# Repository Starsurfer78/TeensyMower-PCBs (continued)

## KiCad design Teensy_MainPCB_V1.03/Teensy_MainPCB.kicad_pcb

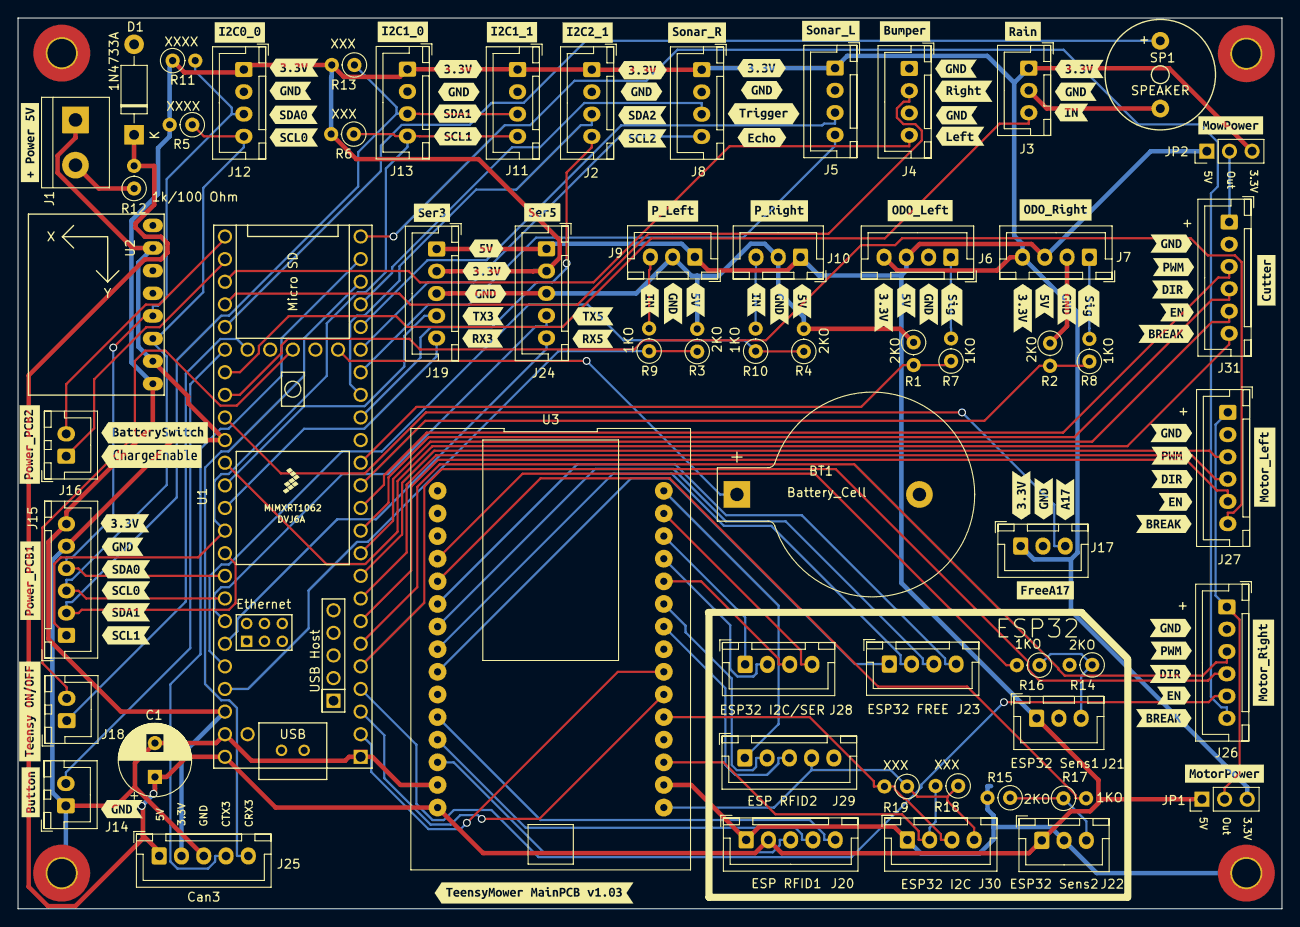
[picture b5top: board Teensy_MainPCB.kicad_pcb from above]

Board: 2 copper layers, 141.9 x 100.0 mm, 160 parts (0 on the bottom side), 76 nets.

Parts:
BT1: Battery_Cell; BatteryHolder_Keystone_103_1x20mm
C1: CP1; CP_Radial_D8.0mm_P3.80mm
D1: 1N4733A; D_DO-41_SOD81_P10.16mm_Horizontal
H1, H2, H3, H4: MountingHole_Pad; MountingHole_3.2mm_M3_Pad_TopBottom
J1: 5V IN; TerminalBlock_bornier-2_P5.08mm
J2: I2C2_0; JST_XH_B4B-XH-A_1x04_P2.50mm_Vertical
J3: Rain; JST_XH_B3B-XH-A_1x03_P2.50mm_Vertical
J4: Bumper; JST_XH_B4B-XH-A_1x04_P2.50mm_Vertical
J5: Sonar_L; JST_XH_B4B-XH-A_1x04_P2.50mm_Vertical
J6: ODO_Left; JST_XH_B4B-XH-A_1x04_P2.50mm_Vertical
J7: ODO_Right; JST_XH_B4B-XH-A_1x04_P2.50mm_Vertical
J8: Sonar_R; JST_XH_B4B-XH-A_1x04_P2.50mm_Vertical
J9: P_Left; JST_XH_B3B-XH-A_1x03_P2.50mm_Vertical
J10: P_Right; JST_XH_B3B-XH-A_1x03_P2.50mm_Vertical
J11: I2C1_1; JST_XH_B4B-XH-A_1x04_P2.50mm_Vertical
J12: I2C0_0; JST_XH_B4B-XH-A_1x04_P2.50mm_Vertical
J13: I2C1_0; JST_XH_B4B-XH-A_1x04_P2.50mm_Vertical
J14: Button; JST_XH_B2B-XH-A_1x02_P2.50mm_Vertical
J15: Power_PCB1; JST_XH_B6B-XH-A_1x06_P2.50mm_Vertical
J16: Power_PCB2; JST_XH_B2B-XH-A_1x02_P2.50mm_Vertical
J17: FreeA17; JST_XH_B3B-XH-A_1x03_P2.50mm_Vertical
J18: Teensy On/Off; JST_XH_B2B-XH-A_1x02_P2.50mm_Vertical
J19: Ser3; JST_XH_B5B-XH-A_1x05_P2.50mm_Vertical
J20: ESP RFID1; JST_XH_B5B-XH-A_1x05_P2.50mm_Vertical
J21: ESP32 Sens1; JST_XH_B3B-XH-A_1x03_P2.50mm_Vertical
J22: ESP32 Sens2; JST_XH_B3B-XH-A_1x03_P2.50mm_Vertical
J23: ESP32 FREE; JST_XH_B4B-XH-A_1x04_P2.50mm_Vertical
J24: Ser5; JST_XH_B5B-XH-A_1x05_P2.50mm_Vertical
J25: Can3; JST_XH_B5B-XH-A_1x05_P2.50mm_Vertical
J26: Motor_Right; JST_XH_B6B-XH-A_1x06_P2.50mm_Vertical
J27: Motor_Left; JST_XH_B6B-XH-A_1x06_P2.50mm_Vertical
J28: ESP32 I2C/SER; JST_XH_B4B-XH-A_1x04_P2.50mm_Vertical
J29: ESP RFID2; JST_XH_B5B-XH-A_1x05_P2.50mm_Vertical
J30: ESP32 I2C; JST_XH_B4B-XH-A_1x04_P2.50mm_Vertical
J31: Cutter; JST_XH_B6B-XH-A_1x06_P2.50mm_Vertical
JP1: MotorPower; PinHeader_1x03_P2.54mm_Vertical
JP2: CutterPower; PinHeader_1x03_P2.54mm_Vertical
R1, R2, R3, R4, R14, R15: 2KO; R_Axial_DIN0207_L6.3mm_D2.5mm_P2.54mm_Vertical
R5, R11: XXXX; R_Axial_DIN0207_L6.3mm_D2.5mm_P2.54mm_Vertical
R6, R13, R18, R19: XXX; R_Axial_DIN0207_L6.3mm_D2.5mm_P2.54mm_Vertical
R7, R8, R9, R10, R16, R17: 1KO; R_Axial_DIN0207_L6.3mm_D2.5mm_P2.54mm_Vertical
R12: 1k/100 Ohm; R_Axial_DIN0207_L6.3mm_D2.5mm_P2.54mm_Vertical
SP1: SPEAKER; Buzzer_12x9.5RM7.6
U1: Teensy4.1; Teensy41
U2: GY-521
U3: ESP32-DEVKIT-V1
kibuzzard-62AA1DDF: G***; kibuzzard-62AA1DDF
kibuzzard-62AA1E85: G***; kibuzzard-62AA1E85
kibuzzard-62AA1F05: G***; kibuzzard-62AA1F05
kibuzzard-62AA3A43: G***; kibuzzard-62AA3A43
kibuzzard-62AA3A85: G***; kibuzzard-62AA3A85
kibuzzard-62AA3B12: G***; kibuzzard-62AA3B12
kibuzzard-62AA34D8: G***; kibuzzard-62AA34D8
kibuzzard-62AA39DC: G***; kibuzzard-62AA39DC
kibuzzard-62AA347B: G***; kibuzzard-62AA347B
kibuzzard-62AA353C: G***; kibuzzard-62AA353C
kibuzzard-62AA3447: G***; kibuzzard-62AA3447
kibuzzard-62AA3566: G***; kibuzzard-62AA3566
kibuzzard-62AB5E06: G***; kibuzzard-62AB5E06
kibuzzard-62AB5E66: G***; kibuzzard-62AB5E66
kibuzzard-62AB5ED1: G***; kibuzzard-62AB5ED1
kibuzzard-62AB5F2F: G***; kibuzzard-62AB5F2F
kibuzzard-62AB5F67: G***; kibuzzard-62AB5F67
kibuzzard-62AB5FC4: G***; kibuzzard-62AB5FC4
kibuzzard-62AB5FF2: G***; kibuzzard-62AB5FF2
kibuzzard-62AB6A77: G***; kibuzzard-62AB6A77
kibuzzard-62AB6A93: G***; kibuzzard-62AB6A93
kibuzzard-62AB6AFA: G***; kibuzzard-62AB6AFA
kibuzzard-62AB6B3D: G***; kibuzzard-62AB6B3D
kibuzzard-62AB6B9B: G***; kibuzzard-62AB6B9B
kibuzzard-62AB6BA8: G***; kibuzzard-62AB6BA8
kibuzzard-62AB6BF4: G***; kibuzzard-62AB6BF4
kibuzzard-62AB6CC8: G***; kibuzzard-62AB6CC8
kibuzzard-62AB6D7A: G***; kibuzzard-62AB6D7A
kibuzzard-62AB6EF0: G***; kibuzzard-62AB6EF0
kibuzzard-62AB6F91: G***; kibuzzard-62AB6F91
kibuzzard-62AB60B1: G***; kibuzzard-62AB60B1
kibuzzard-62AB62B6: G***; kibuzzard-62AB62B6
kibuzzard-62AB62D3: G***; kibuzzard-62AB62D3
kibuzzard-62AB63D2: G***; kibuzzard-62AB63D2
kibuzzard-62AB64C2: G***; kibuzzard-62AB64C2
kibuzzard-62AB64F2: G***; kibuzzard-62AB64F2
kibuzzard-62AB77E5: G***; kibuzzard-62AB77E5
kibuzzard-62AB634F: G***; kibuzzard-62AB634F
kibuzzard-62AB639B: G***; kibuzzard-62AB639B
kibuzzard-62AB756D: G***; kibuzzard-62AB756D
kibuzzard-62AB767F: G***; kibuzzard-62AB767F
kibuzzard-62AB774A: G***; kibuzzard-62AB774A
kibuzzard-62AB778D: G***; kibuzzard-62AB778D
kibuzzard-62AB789F: G***; kibuzzard-62AB789F
kibuzzard-62AB6021: G***; kibuzzard-62AB6021
kibuzzard-62AB6109: G***; kibuzzard-62AB6109
kibuzzard-62AB6374: G***; kibuzzard-62AB6374
kibuzzard-62AB6557: G***; kibuzzard-62AB6557
kibuzzard-62AB7031: G***; kibuzzard-62AB7031
kibuzzard-62AC4CEE: G***; kibuzzard-62AC4CEE
kibuzzard-62AC4D6D: G***; kibuzzard-62AC4D6D
kibuzzard-62AC8CBD: G***; kibuzzard-62AC8CBD
kibuzzard-62AC8CC8: G***; kibuzzard-62AC8CC8
kibuzzard-62AC8CD7: G***; kibuzzard-62AC8CD7
kibuzzard-62AC8CE7: G***; kibuzzard-62AC8CE7
kibuzzard-62AC8CFB: G***; kibuzzard-62AC8CFB
kibuzzard-62AC8D1B: G***; kibuzzard-62AC8D1B
kibuzzard-62AC8D10: G***; kibuzzard-62AC8D10
kibuzzard-62AC8D87: G***; kibuzzard-62AC8D87
kibuzzard-62AC8DAF: G***; kibuzzard-62AC8DAF
kibuzzard-62AC8DEE: G***; kibuzzard-62AC8DEE
kibuzzard-62AC8E7D: G***; kibuzzard-62AC8E7D
kibuzzard-62AC8E96: G***; kibuzzard-62AC8E96
kibuzzard-62AC8EE6: G***; kibuzzard-62AC8EE6
kibuzzard-62AC8F0E: G***; kibuzzard-62AC8F0E
kibuzzard-62AC8F57: G***; kibuzzard-62AC8F57
kibuzzard-62AC8F80: G***; kibuzzard-62AC8F80
kibuzzard-62AC8F92: G***; kibuzzard-62AC8F92
kibuzzard-62AC8FB5: G***; kibuzzard-62AC8FB5
kibuzzard-62AC8FDD: G***; kibuzzard-62AC8FDD
kibuzzard-62AC8FEE: G***; kibuzzard-62AC8FEE
kibuzzard-62AC52F4: G***; kibuzzard-62AC52F4
kibuzzard-62AC90B9: G***; kibuzzard-62AC90B9
kibuzzard-62AC90FB: G***; kibuzzard-62AC90FB
kibuzzard-62AC91A3: G***; kibuzzard-62AC91A3
kibuzzard-62AC91BB: G***; kibuzzard-62AC91BB
kibuzzard-62AC91C5: G***; kibuzzard-62AC91C5
kibuzzard-62AC91DF: G***; kibuzzard-62AC91DF
kibuzzard-62AC91F0: G***; kibuzzard-62AC91F0
kibuzzard-62AC92C8: G***; kibuzzard-62AC92C8
kibuzzard-62AC93D0: G***; kibuzzard-62AC93D0
kibuzzard-62AC95A7: G***; kibuzzard-62AC95A7
kibuzzard-62AC95BD: G***; kibuzzard-62AC95BD
kibuzzard-62AC95C9: G***; kibuzzard-62AC95C9
kibuzzard-62AC916E: G***; kibuzzard-62AC916E
kibuzzard-62AC917A: G***; kibuzzard-62AC917A
kibuzzard-62AC918B: G***; kibuzzard-62AC918B
kibuzzard-62AC932E: G***; kibuzzard-62AC932E
kibuzzard-62AC961B: G***; kibuzzard-62AC961B
kibuzzard-62AC9112: G***; kibuzzard-62AC9112
kibuzzard-62AC9161: G***; kibuzzard-62AC9161
kibuzzard-62AC9196: G***; kibuzzard-62AC9196
kibuzzard-62AC9203: G***; kibuzzard-62AC9203
kibuzzard-62AC9315: G***; kibuzzard-62AC9315
kibuzzard-62AC9376: G***; kibuzzard-62AC9376
kibuzzard-62AC9630: G***; kibuzzard-62AC9630
kibuzzard-62AC9639: G***; kibuzzard-62AC9639

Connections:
+3V3: J2.1, J3.1, J5.1, J6.4, J7.4, J8.1, J11.1, J12.1, J13.1, J15.6, J17.1, J19.2, J24.2, J25.2, JP1.3, JP2.3, R5.2, R6.2, R11.1, R13.2, U1.46 (3V3), U2.1 (VCC)
+5V: C1.1, D1.1 (K), J6.3, J7.3, J9.1, J10.1, J19.1, J20.2, J21.1, J22.1, J24.1, J25.1, JP1.1, JP2.1, R12.2, U1.48 (VIN), U3.15 (VIN)
CRX3: J25.5, U1.22 (30_CRX3)
CTX3: J25.4, U1.23 (31_CTX3)
FreeA17: J17.3, U1.33 (41_A17)
GND: BT1.2 (-), C1.2, D1.2 (A), H1.1, H2.1, H3.1, H4.1, J1.1, J2.2, J3.2, J4.1, J4.3, J5.2, J6.2, J7.2, J8.2, J9.2, J10.2, J11.2, J12.2, J13.2, J14.1, J15.5, J17.2, J19.3, J20.1, J21.2, J22.2, J24.3, J25.3, J26.2, J27.2, J30.1, J31.2, R1.1, R2.1, R3.2, R4.2, R14.2, R15.2, SP1.1, U1.1 (GND), U1.34 (GND), U1.47 (GND), U2.2 (GND), U2.7 (AD0), U3.14 (GND), U3.17 (GND)
unnamed: BT1.1 (+), U1.50 (VBAT)
unnamed: J1.2, R12.1
unnamed: J6.1, R7.2
unnamed: J7.1, R8.2
unnamed: J9.3, R9.2
unnamed: J10.3, R10.2
unnamed: J18.1, U1.54 (ON_OFF)
unnamed: J18.2, U1.52 (GND)
unnamed: J20.3, U3.13 (GPIO13_ADC2-CH4_HSPI-MOSI_RTC-GPIO14)
unnamed: J20.4, U3.12 (GPIO12_ADC2-CH5_HSPI-MISO_RTC-GPIO15)
unnamed: J20.5, U3.11 (GPIO14_ADC2-CH6_HSPI-CLK_RTC-GPIO16)
unnamed: J21.3, R14.1, R16.1
unnamed: J22.3, R15.1, R17.1
unnamed: J23.1, U3.9 (GPIO26_ADC2-CH9_DAC2_RTC-GPIO7)
unnamed: J23.2, U3.8 (GPIO25_ADC2-CH8_DAC1_RTC-GPIO6)
unnamed: J23.3, U3.7 (GPIO33_ADC1-CH5_RTC-GPIO8)
unnamed: J23.4, U3.6 (GPIO32_ADC1-CH4_RTC-GPIO9)
unnamed: J26.1, J27.1, JP1.2
unnamed: J28.1, U3.28 (GPIO1_UART0-TX)
unnamed: J28.2, U3.27 (GPIO3__UART0-RX)
unnamed: J28.3, U3.26 (GPIO21_I2C-SDA)
unnamed: J28.4, U3.29 (GPIO22_I2C-SCL)
unnamed: J29.1, U3.30 (GPIO23_VSPI-MOSI)
unnamed: J29.2, U3.25 (GPIO19_VSPI-MISO)
unnamed: J29.3, U3.24 (GPIO18_VSPI-CLK)
unnamed: J29.4, J30.4, R18.1, R19.1, U3.16 (3V3)
unnamed: J30.2, R18.2, U3.18 (GPIO15_ADC2-CH3_HSPI-CS0_RTC-GPIO13)
unnamed: J30.3, R19.2, U3.20 (GPIO4_ADC2-CH0_RTC-GPIO10)
unnamed: J31.1, JP2.2
unnamed: R16.2, U3.4 (GPIO34_ADC1-CH6_RTC-GPIO4)
unnamed: R17.2, U3.5 (GPIO35_ADC1-CH7_RTC-GPIO5)
RX1: U1.2 (0_RX1_CRX2_CS1), U3.22 (TX2)
RX3: J19.5, U1.37 (15_A1_RX3_SPDIF_IN)
RX5: J24.5, U1.43 (21_A7_RX5_BCLK1)
SCL0: J12.4, J15.3, R5.1, U1.41 (19_A5_SCL), U2.3 (SCL)
SCL1: J11.4, J13.4, J15.1, R6.1, U1.38 (16_A2_RX4_SCL1)
SCL2: J2.4, U1.16 (24_A10_TX6_SCL2)
SDA0: J12.3, J15.4, R11.2, U1.40 (18_A4_SDA), U2.4 (SDA)
SDA1: J11.3, J13.3, J15.2, R13.1, U1.39 (17_A3_TX4_SDA1)
SDA2: J2.3, U1.17 (25_A11_RX6_SDA2)
TX1: U1.3 (1_TX1_CTX2_MISO1), U3.21 (RX2)
TX3: J19.4, U1.36 (14_A0_TX3_SPDIF_OUT)
TX5: J24.4, U1.42 (20_A6_TX5_LRCLK1)
pinBatterySwitch: J16.2, U1.25 (33_MCLK2)
pinBumperLeft: J4.4, U1.27 (35_TX8)
pinBumperRight: J4.2, U1.28 (36_CS)
pinButton: J14.2, U1.30 (38_CS1_IN1)
pinBuzzer: SP1.2, U1.29 (37_CS)
pinChargeEnable: J16.1, U1.26 (34_RX8)
pinMotorLeftBreak: J27.6, U1.32 (40_A16)
pinMotorLeftDir: J27.4, U1.8 (6_OUT1D)
pinMotorLeftEnable: J27.5, U1.7 (5_IN2)
pinMotorLeftPWM: J27.3, U1.9 (7_RX2_OUT1A)
pinMotorMowBreak: J31.6, U1.35 (13_SCK_LED)
pinMotorMowDir: J31.4, U1.11 (9_OUT1C)
pinMotorMowEnable: J31.5, U1.10 (8_TX2_IN1)
pinMotorMowPWM: J31.3, U1.12 (10_CS_MQSR)
pinMotorRightBreak: J26.6, U1.24 (32_OUT1B)
pinMotorRightDir: J26.4, U1.5 (3_LRCLK2)
pinMotorRightEnable: J26.5, U1.4 (2_OUT2)
pinMotorRightPWM: J26.3, U1.6 (4_BCLK2)
pinOdometryLeft: R1.2, R7.1, U1.14 (12_MISO_MQSL)
pinOdometryRight: R2.2, R8.1, U1.13 (11_MOSI_CTX1)
pinPerimeterLeft: R3.1, R9.1, U1.45 (23_A9_CRX1_MCLK1)
pinPerimeterRight: R4.1, R10.1, U1.44 (22_A8_CTX1)
pinRain: J3.3, U1.31 (39_MISO1_OUT1A)
pinSonarLeftEcho: J5.4, U1.18 (26_A12_MOSI1)
pinSonarLeftTrigger: J5.3, U1.20 (28_RX7)
pinSonarRightEcho: J8.4, U1.19 (27_A13_SCK1)
pinSonarRightTrigger: J8.3, U1.21 (29_TX7)

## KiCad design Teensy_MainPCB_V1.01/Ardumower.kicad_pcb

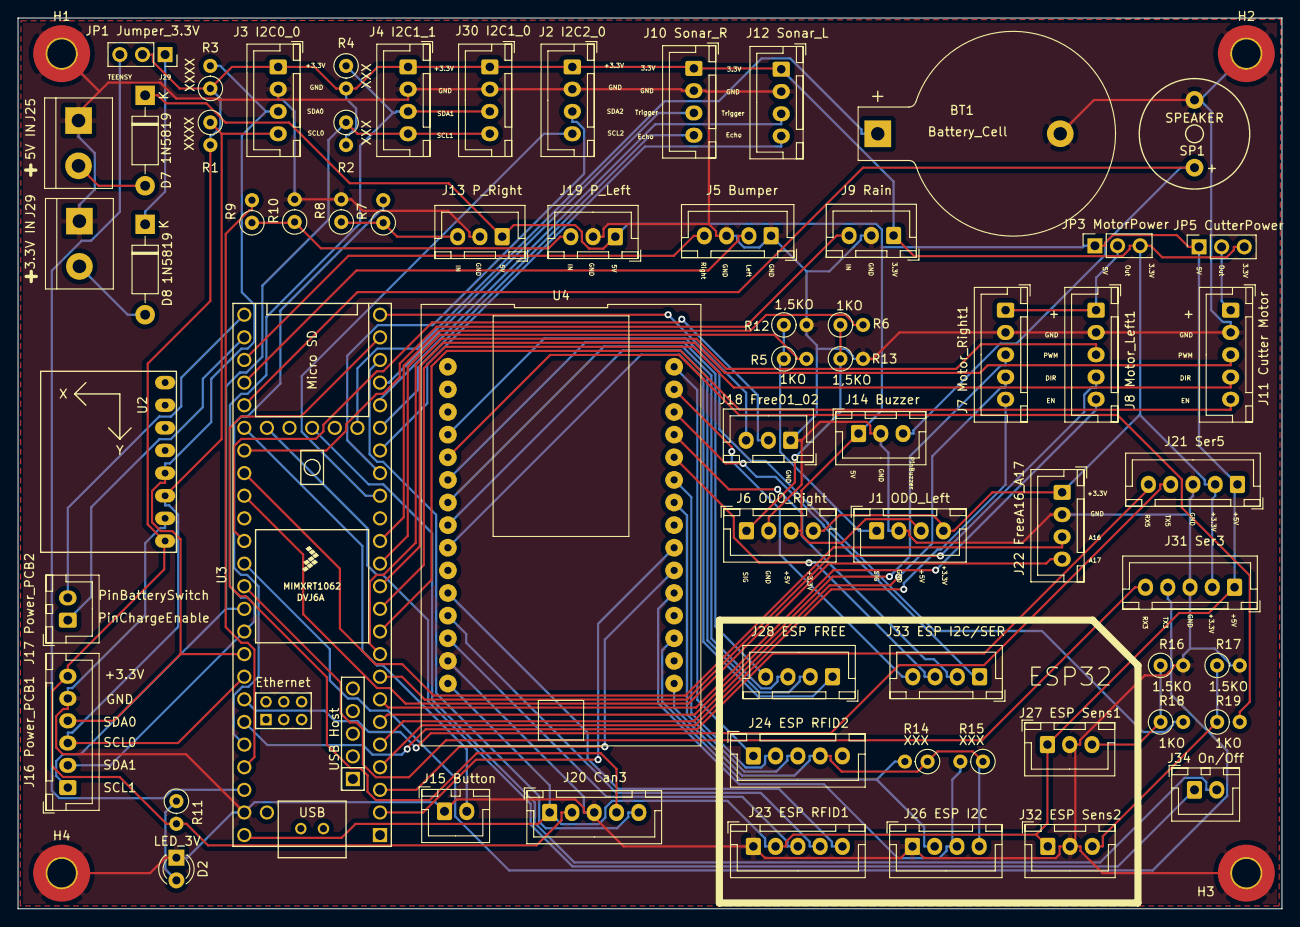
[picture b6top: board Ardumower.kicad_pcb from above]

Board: 2 copper layers, 141.9 x 100.0 mm, 68 parts (0 on the bottom side), 80 nets.

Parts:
BT1: Battery_Cell; BatteryHolder_Keystone_103_1x20mm
D2: LED_3V; LED_D3.0mm
D7, D8: 1N5819; D_DO-41_SOD81_P10.16mm_Horizontal
H1, H2, H3, H4: MountingHole_Pad; MountingHole_3.2mm_M3_Pad_TopBottom
J1 ODO_Left: ODO_Left; JST_XH_B4B-XH-A_1x04_P2.50mm_Vertical
J2 I2C2_0: I2C2_0; JST_XH_B4B-XH-A_1x04_P2.50mm_Vertical
J3 I2C0_0: I2C0_0; JST_XH_B4B-XH-A_1x04_P2.50mm_Vertical
J4 I2C1_1: I2C1_1; JST_XH_B4B-XH-A_1x04_P2.50mm_Vertical
J5 Bumper: Bumper; JST_XH_B4B-XH-A_1x04_P2.50mm_Vertical
J6 ODO_Right: ODO_Right; JST_XH_B4B-XH-A_1x04_P2.50mm_Vertical
J7 Motor_Right1: Motor_Right1; JST_XH_B5B-XH-A_1x05_P2.50mm_Vertical
J8 Motor_Left1: Motor_Left1; JST_XH_B5B-XH-A_1x05_P2.50mm_Vertical
J9 Rain: Rain; JST_XH_B3B-XH-A_1x03_P2.50mm_Vertical
J10 Sonar_R: Sonar_R; JST_XH_B4B-XH-A_1x04_P2.50mm_Vertical
J11 Cutter Motor: Cutter; JST_XH_B5B-XH-A_1x05_P2.50mm_Vertical
J12 Sonar_L: Sonar_L; JST_XH_B4B-XH-A_1x04_P2.50mm_Vertical
J13 P_Right: P_Right; JST_XH_B3B-XH-A_1x03_P2.50mm_Vertical
J14 Buzzer: Buzzer; JST_XH_B3B-XH-A_1x03_P2.50mm_Vertical
J15 Button: Button; JST_XH_B2B-XH-A_1x02_P2.50mm_Vertical
J16 Power_PCB1: Power_PCB1; JST_XH_B6B-XH-A_1x06_P2.50mm_Vertical
J17 Power_PCB2: Power_PCB2; JST_XH_B2B-XH-A_1x02_P2.50mm_Vertical
J18 Free01_02: Free01_02; JST_XH_B3B-XH-A_1x03_P2.50mm_Vertical
J19 P_Left: P_Left; JST_XH_B3B-XH-A_1x03_P2.50mm_Vertical
J20 Can3: Can3; JST_XH_B5B-XH-A_1x05_P2.50mm_Vertical
J21 Ser5: Ser5; JST_XH_B5B-XH-A_1x05_P2.50mm_Vertical
J22 FreeA16_A17: FreeA16_A17; JST_XH_B4B-XH-A_1x04_P2.50mm_Vertical
J23 ESP RFID1: ESP RFID1; JST_XH_B5B-XH-A_1x05_P2.50mm_Vertical
J24 ESP RFID2: ESP RFID2; JST_XH_B5B-XH-A_1x05_P2.50mm_Vertical
J25: 5V IN; TerminalBlock_bornier-2_P5.08mm
J26 ESP I2C: ESP32 I2C; JST_XH_B4B-XH-A_1x04_P2.50mm_Vertical
J27 ESP Sens1: ESP32 Sens1; JST_XH_B3B-XH-A_1x03_P2.50mm_Vertical
J28 ESP FREE: ESP32 FREE; JST_XH_B4B-XH-A_1x04_P2.50mm_Vertical
J29: 3.3V IN; TerminalBlock_bornier-2_P5.08mm
J30 I2C1_0: I2C1_0; JST_XH_B4B-XH-A_1x04_P2.50mm_Vertical
J31 Ser3: Ser3; JST_XH_B5B-XH-A_1x05_P2.50mm_Vertical
J32 ESP Sens2: ESP32 Sens2; JST_XH_B3B-XH-A_1x03_P2.50mm_Vertical
J33 ESP I2C/SER: ESP32 I2C/SER; JST_XH_B4B-XH-A_1x04_P2.50mm_Vertical
J34 On/Off: Teensy On/Off; JST_XH_B2B-XH-A_1x02_P2.50mm_Vertical
JP1 Jumper_3.3V: Jumper_3.3V; PinSocket_1x03_P2.54mm_Vertical
JP3 MotorPower: MotorPower; PinSocket_1x03_P2.54mm_Vertical
JP5 CutterPower: CutterPower; PinSocket_1x03_P2.54mm_Vertical
R1, R3: XXXX; R_Axial_DIN0207_L6.3mm_D2.5mm_P2.54mm_Vertical
R2, R4, R14, R15: XXX; R_Axial_DIN0207_L6.3mm_D2.5mm_P2.54mm_Vertical
R5, R6, R7, R9, R18, R19: 1KO; R_Axial_DIN0207_L6.3mm_D2.5mm_P2.54mm_Vertical
R8, R10, R16, R17: 1.5KO; R_Axial_DIN0207_L6.3mm_D2.5mm_P2.54mm_Vertical
R11: 100; R_Axial_DIN0207_L6.3mm_D2.5mm_P2.54mm_Vertical
R12, R13: 1,5KO; R_Axial_DIN0207_L6.3mm_D2.5mm_P2.54mm_Vertical
SP1: SPEAKER; Buzzer_12x9.5RM7.6
U2: GY-521
U3: Teensy4.1; Teensy41
U4: ESP32-DEVKIT-V1

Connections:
+3V3: J1 ODO_Left.4, J2 I2C2_0.1, J3 I2C0_0.1, J4 I2C1_1.1, J6 ODO_Right.4, J9 Rain.1, J10 Sonar_R.1, J12 Sonar_L.1, J16 Power_PCB1.6, J20 Can3.2, J21 Ser5.2, J22 FreeA16_A17.1, J30 I2C1_0.1, J31 Ser3.2, JP1 Jumper_3.3V.2, JP3 MotorPower.3, JP5 CutterPower.3, R1.2, R2.2, R3.1, R4.2, R11.2, U2.1
+5V: D7.1, J1 ODO_Left.3, J6 ODO_Right.3, J13 P_Right.1, J14 Buzzer.1, J19 P_Left.1, J20 Can3.1, J21 Ser5.1, J23 ESP RFID1.2, J27 ESP Sens1.1, J31 Ser3.1, J32 ESP Sens2.1, JP3 MotorPower.1, JP5 CutterPower.1, U3.48, U4.15
CRX3: J20 Can3.5, U3.22
CTX3: J20 Can3.4, U3.23
Free01: J18 Free01_02.2, U3.35
Free02: J18 Free01_02.3, U3.24
FreeA16: J22 FreeA16_A17.3, U3.32
FreeA17: J22 FreeA16_A17.4, U3.33
GND: BT1.2, D2.1, H1.1, H2.1, H3.1, H4.1, J1 ODO_Left.2, J2 I2C2_0.2, J3 I2C0_0.2, J4 I2C1_1.2, J5 Bumper.1, J5 Bumper.3, J6 ODO_Right.2, J7 Motor_Right1.2, J8 Motor_Left1.2, J9 Rain.2, J10 Sonar_R.2, J11 Cutter Motor.2, J12 Sonar_L.2, J13 P_Right.2, J14 Buzzer.2, J15 Button.1, J16 Power_PCB1.5, J18 Free01_02.1, J19 P_Left.2, J20 Can3.3, J21 Ser5.3, J22 FreeA16_A17.2, J23 ESP RFID1.1, J25.1, J26 ESP I2C.1, J27 ESP Sens1.2, J29.1, J30 I2C1_0.2, J31 Ser3.3, J32 ESP Sens2.2, R8.2, R10.2, R12.2, R13.2, R16.2, R17.2, SP1.1, U2.2, U3.47, U4.14
unnamed: BT1.1, U3.50
unnamed: D2.2, R11.1
unnamed: D7.2, J25.2
unnamed: D8.1, JP1 Jumper_3.3V.1
unnamed: D8.2, J29.2
unnamed: J1 ODO_Left.1, R5.1, R12.1
unnamed: J6 ODO_Right.1, R6.1, R13.1
unnamed: J7 Motor_Right1.1, J8 Motor_Left1.1, JP3 MotorPower.2
unnamed: J11 Cutter Motor.1, JP5 CutterPower.2
unnamed: J13 P_Right.3, R7.1, R8.1
unnamed: J19 P_Left.3, R9.1, R10.1
unnamed: J23 ESP RFID1.3, U4.13
unnamed: J23 ESP RFID1.4, U4.12
unnamed: J23 ESP RFID1.5, U4.11
unnamed: J24 ESP RFID2.1, U4.30
unnamed: J24 ESP RFID2.2, U4.25
unnamed: J24 ESP RFID2.3, U4.24
unnamed: J24 ESP RFID2.4, J26 ESP I2C.4, R14.1, R15.1, U4.16
unnamed: J26 ESP I2C.2, R14.2, U4.18
unnamed: J26 ESP I2C.3, R15.2, U4.20
unnamed: J27 ESP Sens1.3, R16.1, R18.1
unnamed: J28 ESP FREE.1, U4.9
unnamed: J28 ESP FREE.2, U4.8
unnamed: J28 ESP FREE.3, U4.7
unnamed: J28 ESP FREE.4, U4.6
unnamed: J32 ESP Sens2.3, R17.1, R19.1
unnamed: J33 ESP I2C/SER.1, U4.28
unnamed: J33 ESP I2C/SER.2, U4.27
unnamed: J33 ESP I2C/SER.3, U4.26
unnamed: J33 ESP I2C/SER.4, U4.29
unnamed: J34 On/Off.1, U3.54
unnamed: J34 On/Off.2, U3.52
unnamed: JP1 Jumper_3.3V.3, U3.46
unnamed: R18.2, U4.4
unnamed: R19.2, U4.5
RX1: U3.2, U4.22
RX3: J31 Ser3.5, U3.37
RX5: J21 Ser5.5, U3.43
SCL0: J3 I2C0_0.4, J16 Power_PCB1.3, R1.1, U2.3, U3.41
SCL1: J4 I2C1_1.4, J16 Power_PCB1.1, J30 I2C1_0.4, R2.1, U3.38
SCL2: J2 I2C2_0.4, U3.16
SDA0: J3 I2C0_0.3, J16 Power_PCB1.4, R3.2, U2.4, U3.40
SDA1: J4 I2C1_1.3, J16 Power_PCB1.2, J30 I2C1_0.3, R4.1, U3.39
SDA2: J2 I2C2_0.3, U3.17
TX1: U3.3, U4.21
TX3: J31 Ser3.4, U3.36
TX5: J21 Ser5.4, U3.42
pinBatterySwitch: J17 Power_PCB2.2, U3.25
pinBumperLeft: J5 Bumper.4, U3.27
pinBumperRight: J5 Bumper.2, U3.28
pinButton: J15 Button.2, U3.30
pinBuzzer: J14 Buzzer.3, SP1.2, U3.29
pinChargeEnable: J17 Power_PCB2.1, U3.26
pinMotorLeftDir: J8 Motor_Left1.4, U3.8
pinMotorLeftEnable: J8 Motor_Left1.5, U3.7
pinMotorLeftPWM: J8 Motor_Left1.3, U3.9
pinMotorMowDir: J11 Cutter Motor.4, U3.11
pinMotorMowEnable: J11 Cutter Motor.5, U3.10
pinMotorMowPWM: J11 Cutter Motor.3, U3.12
pinMotorRightDir: J7 Motor_Right1.4, U3.5
pinMotorRightEnable: J7 Motor_Right1.5, U3.4
pinMotorRightPWM: J7 Motor_Right1.3, U3.6
pinOdometryLeft: R6.2, U3.14
pinOdometryRight: R5.2, U3.13
pinPerimeterLeft: R9.2, U3.45
pinPerimeterRight: R7.2, U3.44
pinRain: J9 Rain.3, U3.31
pinSonarLeftEcho: J12 Sonar_L.4, U3.18
pinSonarLeftTrigger: J12 Sonar_L.3, U3.20
pinSonarRightEcho: J10 Sonar_R.4, U3.19
pinSonarRightTrigger: J10 Sonar_R.3, U3.21

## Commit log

2021-11-04 Start Commit
    Clean start
2021-11-04 Delete unused Files
    Delete old Files
2021-11-04 Rename Files
    Rename Files
2021-11-29 Small Changes in Layout Text
2021-11-29 Add Pictures
2021-12-04 Add Shopping List
2021-12-04 Remove
2022-02-01 Start Test
2022-02-01 Add Bigger Font
    New Version, with bigger Font. At present still without conductors
2022-02-01 Create _autosave-Teensy_MainPCB.kicad_pcb
    Bigger Font, small sorting changes
2022-02-01 Add Schematic PDF
2022-02-01 Front Correction
2022-02-02 First Route
2022-02-02 Rename Schematic
2022-02-02 Add GND Plane
2022-02-04 Add ESP32 Files
2022-03-04 Small Changes in Labelling
2022-03-05 Removed unused
    Remove unused Items and sorting new
2022-05-13 Add MainPCB v1.03
2022-05-13 Move Gerber Files
2022-05-13 Add PDF and Picture
2022-05-13 Add Revision
2022-05-15 Small changes
2022-06-17 v1.03
2022-06-17 Boom File
2022-06-22 Rework of chargePCB
2022-06-26 Rebuild Charge Board
2022-06-26 Update Schematic PDF
2022-08-28 Don' know anymore
2022-09-03 Add Labeling and PCB Routing
2022-09-03 Removed old Pics
2022-09-03 Start Sender Design
2022-09-03 Start Design of Sender
2022-09-15 Add Gerber Files
2022-09-15 removed Files
2022-12-20 Add Tracks
    Tracks added
2023-03-02 Add BOM File
2023-04-02 Wifi Sender Update Label
2023-04-02 Add Sender Image
2023-04-02 Update README.md
    Update Readme
2023-04-12 Start PowerPCB_v1.08
2023-04-24 Routing and change some Places
2023-04-28 Change Diode
2023-05-02 Routing and Gerber Files
2023-05-02 Add Boom File
2023-05-14 Connection from jumper changed
2023-05-16 Add MBR1045
2023-09-01 No Changes
2023-12-05 Update PDF, Picture, Route
    Update the PDF File of the Board.
    Update PCB Picture.
    Route the PCB
2023-12-05 Remove v1.08 PCB is Scrap
2023-12-05 Add some Logos to PCB
2024-02-07 Wrong Direktion of Q2 and Q4
    The Drain and Source Pin was in the wrong direction.
2024-02-08 Small Updates
2024-02-08 Change SDA SCL Footprint
    Ad new Schematic PDF and BOOM File
2024-02-08 Add First SMALL PowerPCB
2024-02-08 Remove unused File
